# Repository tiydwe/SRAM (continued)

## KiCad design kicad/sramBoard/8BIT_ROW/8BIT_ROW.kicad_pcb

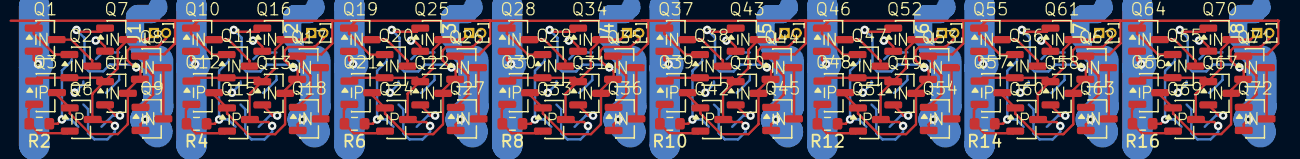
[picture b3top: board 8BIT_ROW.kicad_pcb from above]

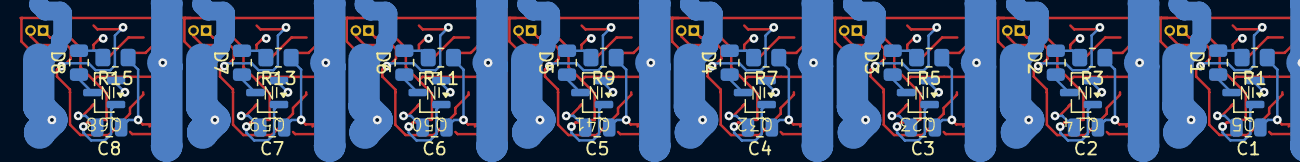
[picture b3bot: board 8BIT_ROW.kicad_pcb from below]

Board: 4 copper layers, 112 parts (32 on the bottom side), 59 nets.

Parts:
C1, C2, C3, C4, C5, C6, C7, C8: 100nC; C_0805_2012Metric
D1, D2, D3, D4, D5, D6, D7, D8: LED; C_0805_2012Metric
J1, J2, J3, J4, J5, J6, J7, J8: Conn_01x02_Pin; PinHeader_1x02_P1.00mm_Vertical
Q1, Q2, Q4, Q5, Q7, Q8, Q9, Q10, Q11, Q13, Q14, Q16, Q17, Q18, Q19, Q20, Q22, Q23, Q25, Q26, Q27, Q28, Q29, Q31, Q32, Q34, Q35, Q36, Q37, Q38, Q40, Q41, Q43, Q44, Q45, Q46, Q47, Q49, Q50, Q52, Q53, Q54, Q55, Q56, Q58, Q59, Q61, Q62, Q63, Q64, Q65, Q67, Q68, Q70, Q71, Q72: Q_NMOS_GSD; SOT-23-N
Q3, Q6, Q12, Q15, Q21, Q24, Q30, Q33, Q39, Q42, Q48, Q51, Q57, Q60, Q66, Q69: Q_PMOS_GSD; SOT-23-P
R1, R3, R5, R7, R9, R11, R13, R15: 360R; R_0805_2012Metric_Pad1.20x1.40mm_HandSolder
R2, R4, R6, R8, R10, R12, R14, R16: 47R; R_0603_1608Metric

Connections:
+5V: C1.1, C2.1, C3.1, C4.1, C5.1, C6.1, C7.1, C8.1, R1.1, R2.1, R3.1, R4.1, R5.1, R6.1, R7.1, R8.1, R9.1, R10.1, R11.1, R12.1, R13.1, R14.1, R15.1, R16.1
/WL: Q1.1 (G), Q2.1 (G), Q8.1 (G), Q9.1 (G), Q10.1 (G), Q11.1 (G), Q17.1 (G), Q18.1 (G), Q19.1 (G), Q20.1 (G), Q26.1 (G), Q27.1 (G), Q28.1 (G), Q29.1 (G), Q35.1 (G), Q36.1 (G), Q37.1 (G), Q38.1 (G), Q44.1 (G), Q45.1 (G), Q46.1 (G), Q47.1 (G), Q53.1 (G), Q54.1 (G), Q55.1 (G), Q56.1 (G), Q62.1 (G), Q63.1 (G), Q64.1 (G), Q65.1 (G), Q71.1 (G), Q72.1 (G)
GND: C1.2, C2.2, C3.2, C4.2, C5.2, C6.2, C7.2, C8.2, Q4.2 (S), Q5.2 (S), Q7.2 (S), Q13.2 (S), Q14.2 (S), Q16.2 (S), Q22.2 (S), Q23.2 (S), Q25.2 (S), Q31.2 (S), Q32.2 (S), Q34.2 (S), Q40.2 (S), Q41.2 (S), Q43.2 (S), Q49.2 (S), Q50.2 (S), Q52.2 (S), Q58.2 (S), Q59.2 (S), Q61.2 (S), Q67.2 (S), Q68.2 (S), Q70.2 (S)
unnamed: D1.2 (A), R1.2
unnamed: D1.1 (K), Q5.3 (D)
unnamed: D2.2 (A), R3.2
unnamed: D2.1 (K), Q14.3 (D)
unnamed: D3.2 (A), R5.2
unnamed: D3.1 (K), Q23.3 (D)
unnamed: D4.2 (A), R7.2
unnamed: D4.1 (K), Q32.3 (D)
unnamed: D5.2 (A), R9.2
unnamed: D5.1 (K), Q41.3 (D)
unnamed: D6.2 (A), R11.2
unnamed: D6.1 (K), Q50.3 (D)
unnamed: D7.2 (A), R13.2
unnamed: D7.1 (K), Q59.3 (D)
unnamed: D8.2 (A), R15.2
unnamed: D8.1 (K), Q68.3 (D)
unnamed: J1.1, Q2.2 (S), Q3.1 (G), Q4.1 (G), Q5.1 (G), Q6.3 (D), Q7.3 (D)
unnamed: J1.2, Q3.3 (D), Q4.3 (D), Q6.1 (G), Q7.1 (G), Q8.2 (S)
unnamed: J2.1, Q11.2 (S), Q12.1 (G), Q13.1 (G), Q14.1 (G), Q15.3 (D), Q16.3 (D)
unnamed: J2.2, Q12.3 (D), Q13.3 (D), Q15.1 (G), Q16.1 (G), Q17.2 (S)
unnamed: J3.1, Q20.2 (S), Q21.1 (G), Q22.1 (G), Q23.1 (G), Q24.3 (D), Q25.3 (D)
unnamed: J3.2, Q21.3 (D), Q22.3 (D), Q24.1 (G), Q25.1 (G), Q26.2 (S)
unnamed: J4.1, Q29.2 (S), Q30.1 (G), Q31.1 (G), Q32.1 (G), Q33.3 (D), Q34.3 (D)
unnamed: J4.2, Q30.3 (D), Q31.3 (D), Q33.1 (G), Q34.1 (G), Q35.2 (S)
unnamed: J5.1, Q38.2 (S), Q39.1 (G), Q40.1 (G), Q41.1 (G), Q42.3 (D), Q43.3 (D)
unnamed: J5.2, Q39.3 (D), Q40.3 (D), Q42.1 (G), Q43.1 (G), Q44.2 (S)
unnamed: J6.1, Q47.2 (S), Q48.1 (G), Q49.1 (G), Q50.1 (G), Q51.3 (D), Q52.3 (D)
unnamed: J6.2, Q48.3 (D), Q49.3 (D), Q51.1 (G), Q52.1 (G), Q53.2 (S)
unnamed: J7.1, Q56.2 (S), Q57.1 (G), Q58.1 (G), Q59.1 (G), Q60.3 (D), Q61.3 (D)
unnamed: J7.2, Q57.3 (D), Q58.3 (D), Q60.1 (G), Q61.1 (G), Q62.2 (S)
unnamed: J8.1, Q65.2 (S), Q66.1 (G), Q67.1 (G), Q68.1 (G), Q69.3 (D), Q70.3 (D)
unnamed: J8.2, Q66.3 (D), Q67.3 (D), Q69.1 (G), Q70.1 (G), Q71.2 (S)
unnamed: Q1.3 (D), Q2.3 (D)
unnamed: Q3.2 (S), Q6.2 (S), R2.2
unnamed: Q8.3 (D), Q9.3 (D)
unnamed: Q10.3 (D), Q11.3 (D)
unnamed: Q12.2 (S), Q15.2 (S), R4.2
unnamed: Q17.3 (D), Q18.3 (D)
unnamed: Q19.3 (D), Q20.3 (D)
unnamed: Q21.2 (S), Q24.2 (S), R6.2
unnamed: Q26.3 (D), Q27.3 (D)
unnamed: Q28.3 (D), Q29.3 (D)
unnamed: Q30.2 (S), Q33.2 (S), R8.2
unnamed: Q35.3 (D), Q36.3 (D)
unnamed: Q37.3 (D), Q38.3 (D)
unnamed: Q39.2 (S), Q42.2 (S), R10.2
unnamed: Q44.3 (D), Q45.3 (D)
unnamed: Q46.3 (D), Q47.3 (D)
unnamed: Q48.2 (S), Q51.2 (S), R12.2
unnamed: Q53.3 (D), Q54.3 (D)
unnamed: Q55.3 (D), Q56.3 (D)
unnamed: Q57.2 (S), Q60.2 (S), R14.2
unnamed: Q62.3 (D), Q63.3 (D)
unnamed: Q64.3 (D), Q65.3 (D)
unnamed: Q66.2 (S), Q69.2 (S), R16.2
unnamed: Q71.3 (D), Q72.3 (D)

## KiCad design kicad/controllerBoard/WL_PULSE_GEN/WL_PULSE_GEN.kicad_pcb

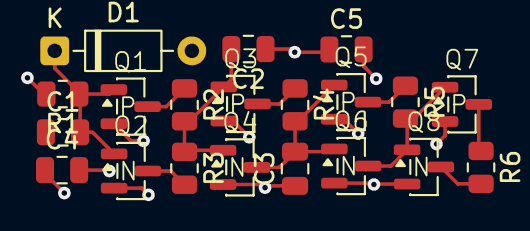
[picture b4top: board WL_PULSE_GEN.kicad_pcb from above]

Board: 2 copper layers, 20 parts (0 on the bottom side), 12 nets.

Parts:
C1, C2, C4, C5: 100nC; C_0805_2012Metric
C3: 4.7uC; C_0805_2012Metric
D1: 1N4148; D_DO-35_SOD27_P7.62mm_Horizontal
Q1, Q3, Q5, Q7: Q_PMOS_GSD; SOT-23-P
Q2, Q4, Q6, Q8: Q_NMOS_GSD; SOT-23-N
R1: 100kR; R_0805_2012Metric
R2, R5: 47R; R_0805_2012Metric
R3, R6: 4.7R; R_0805_2012Metric
R4: 4.7kR; R_0805_2012Metric

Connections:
+5V: C4.2, C5.2, Q1.2 (S), Q3.2 (S), Q5.2 (S), Q7.2 (S)
/WL_PULSE: Q8.3 (D), R6.2
GND: C2.1, C3.1, C4.1, C5.1, D1.2 (A), Q2.2 (S), Q4.2 (S), Q6.2 (S), Q8.2 (S), R1.2
unnamed: C1.2, D1.1 (K), Q1.1 (G), Q2.1 (G), R1.1
unnamed: Q1.3 (D), R2.1
unnamed: Q2.3 (D), R3.2
unnamed: Q3.3 (D), R4.1
unnamed: C2.2, Q3.1 (G), Q4.1 (G), R2.2, R3.1
unnamed: C3.2, Q4.3 (D), Q5.1 (G), Q6.1 (G), R4.2
unnamed: Q5.3 (D), R5.1
unnamed: Q6.3 (D), Q7.1 (G), Q8.1 (G), R5.2
unnamed: Q7.3 (D), R6.1

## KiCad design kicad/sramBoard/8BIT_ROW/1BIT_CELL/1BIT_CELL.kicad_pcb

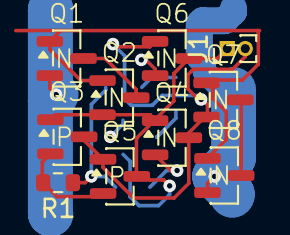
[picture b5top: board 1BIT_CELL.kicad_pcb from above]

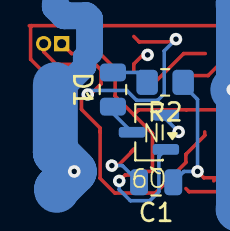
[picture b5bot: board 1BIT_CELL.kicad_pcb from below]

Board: 4 copper layers, 14 parts (4 on the bottom side), 10 nets.

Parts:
C1: 100nC; C_0805_2012Metric
D1: LED; C_0805_2012Metric
J1: Conn_01x02_Pin; PinHeader_1x02_P1.00mm_Vertical
Q1, Q2, Q4, Q6, Q7, Q8, Q9: Q_NMOS_GSD; SOT-23-N
Q3, Q5: Q_PMOS_GSD; SOT-23-P
R1: 47R; R_0603_1608Metric
R2: 360R; R_0805_2012Metric_Pad1.20x1.40mm_HandSolder

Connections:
+5V: C1.1, R1.1, R2.1
/WL: Q1.1 (G), Q2.1 (G), Q7.1 (G), Q8.1 (G)
GND: C1.2, Q4.2 (S), Q6.2 (S), Q9.2 (S)
unnamed: D1.2 (A), R2.2
unnamed: D1.1 (K), Q9.3 (D)
unnamed: J1.1, Q2.2 (S), Q3.1 (G), Q4.1 (G), Q5.3 (D), Q6.3 (D), Q9.1 (G)
unnamed: J1.2, Q3.3 (D), Q4.3 (D), Q5.1 (G), Q6.1 (G), Q7.2 (S)
unnamed: Q1.3 (D), Q2.3 (D)
unnamed: Q3.2 (S), Q5.2 (S), R1.2
unnamed: Q7.3 (D), Q8.3 (D)

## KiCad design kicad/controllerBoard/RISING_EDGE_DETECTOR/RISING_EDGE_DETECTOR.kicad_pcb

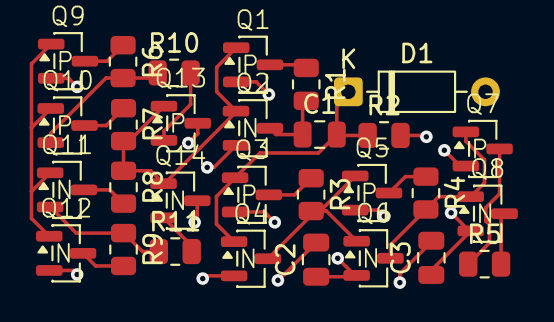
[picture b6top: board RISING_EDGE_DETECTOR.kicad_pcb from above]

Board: 2 copper layers, 29 parts (0 on the bottom side), 21 nets.

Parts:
C1, C2, C3: 100nC; C_0805_2012Metric
D1: 1N4148; D_DO-35_SOD27_P7.62mm_Horizontal
Q1, Q3, Q5, Q7, Q9, Q10, Q13: Q_PMOS_GSD; SOT-23-P
Q2, Q4, Q6, Q8, Q11, Q12, Q14: Q_NMOS_GSD; SOT-23-N
R1, R3, R5, R6, R7, R8, R9: 47R; R_0805_2012Metric
R2: 10kR; R_0805_2012Metric
R4: 1R; R_0805_2012Metric
R10, R11: 10R; R_0805_2012Metric

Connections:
+5V: C2.2, C3.2, Q1.2 (S), Q3.2 (S), Q5.2 (S), Q7.2 (S), Q9.2 (S), Q14.3 (D)
/SCHMITT_TRIGGER/V_{out}: Q1.1 (G), Q2.1 (G), Q13.1 (G), Q14.1 (G), R7.2, R8.1
/V_{in}: Q9.1 (G), Q10.1 (G), Q11.1 (G), Q12.1 (G)
/V_{pulse}: Q6.3 (D), Q7.1 (G), Q8.1 (G), R4.2
/~V_{pulse}: Q8.3 (D), R5.2
GND: C2.1, C3.1, D1.2 (A), Q2.2 (S), Q4.2 (S), Q6.2 (S), Q8.2 (S), Q12.2 (S), Q13.3 (D), R2.2
unnamed: C1.2, D1.1 (K), Q3.1 (G), Q4.1 (G), R2.1
unnamed: Q1.3 (D), R1.1
unnamed: C1.1, Q2.3 (D), R1.2
unnamed: Q3.3 (D), R3.1
unnamed: Q4.3 (D), Q5.1 (G), Q6.1 (G), R3.2
unnamed: Q5.3 (D), R4.1
unnamed: Q7.3 (D), R5.1
unnamed: Q9.3 (D), R6.1
unnamed: Q10.3 (D), R7.1
unnamed: Q10.2 (S), R6.2, R10.1
unnamed: Q11.3 (D), R8.2
unnamed: Q11.2 (S), R9.1, R11.1
unnamed: Q12.3 (D), R9.2
unnamed: Q13.2 (S), R10.2
unnamed: Q14.2 (S), R11.2

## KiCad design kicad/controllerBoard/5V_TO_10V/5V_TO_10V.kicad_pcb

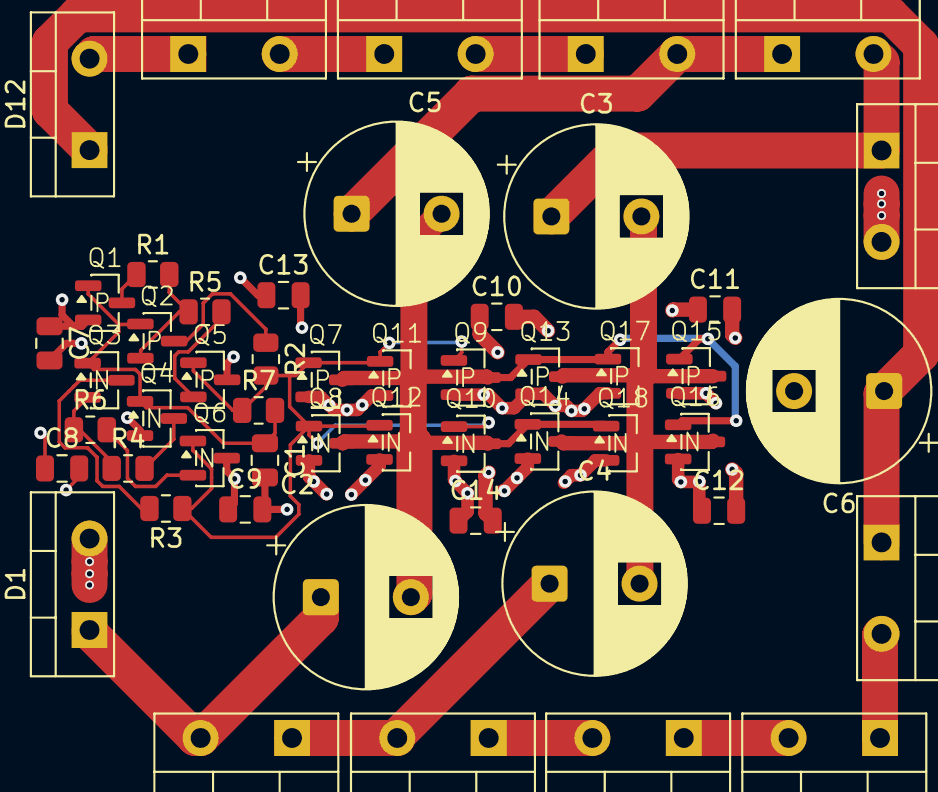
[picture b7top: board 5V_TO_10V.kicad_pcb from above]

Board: 2 copper layers, 51 parts (0 on the bottom side), 25 nets.

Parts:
C1, C7, C8, C9, C10, C11, C12, C13, C14: 100nC; C_0805_2012Metric
C2, C3, C4, C5, C6: C_Polarized; CP_Radial_D10.0mm_P5.00mm
D1, D2, D3, D4, D5, D6, D7, D8, D9, D10, D11, D12: MUR1560FAC; TO-220-2_Vertical
Q1, Q2, Q5, Q7, Q9, Q11, Q13, Q15, Q17: Q_PMOS_GSD; SOT-23-P
Q3, Q4, Q6, Q8, Q10, Q12, Q14, Q16, Q18: Q_NMOS_GSD; SOT-23-N
R1, R2, R3, R4: 47R; R_0805_2012Metric
R5, R6: 1R; R_0805_2012Metric
R7: 470R; R_0805_2012Metric

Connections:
+5V: C7.1, C8.1, C9.1, C10.1, C11.2, C12.2, C13.2, C14.2, D1.2 (A), D2.2 (A), Q1.2 (S), Q6.3 (D), Q7.2 (S), Q9.2 (S), Q11.2 (S), Q13.2 (S), Q15.2 (S), Q17.2 (S)
/10V: C6.1, D11.1 (K), D12.1 (K)
GND: C1.2, C6.2, C7.2, C8.2, C9.2, C10.2, C11.1, C12.1, C13.1, C14.1, Q4.2 (S), Q5.3 (D), Q8.2 (S), Q10.2 (S), Q12.2 (S), Q14.2 (S), Q16.2 (S), Q18.2 (S)
unnamed: C2.1, D1.1 (K), D3.2 (A)
unnamed: C3.1, D2.1 (K), D4.2 (A)
unnamed: C4.1, D3.1 (K), D5.2 (A)
unnamed: C5.1, D4.1 (K), D6.2 (A)
unnamed: D5.1 (K), D7.2 (A)
unnamed: D6.1 (K), D8.2 (A)
unnamed: D7.1 (K), D9.2 (A)
unnamed: D8.1 (K), D10.2 (A)
unnamed: D10.1 (K), D12.2 (A)
unnamed: D9.1 (K), D11.2 (A)
unnamed: Q1.3 (D), R1.1
unnamed: C1.1, Q1.1 (G), Q2.1 (G), Q3.1 (G), Q4.1 (G), R7.2
unnamed: Q2.3 (D), R2.1
unnamed: Q2.2 (S), R1.2, R5.1
unnamed: Q3.3 (D), R3.2
unnamed: Q3.2 (S), R4.1, R6.1
unnamed: Q4.3 (D), R4.2
unnamed: Q5.2 (S), R5.2
unnamed: Q6.2 (S), R6.2
unnamed: C2.2, C5.2, Q7.3 (D), Q8.3 (D), Q9.3 (D), Q10.3 (D), Q11.3 (D), Q12.3 (D), Q13.1 (G), Q14.1 (G), Q15.1 (G), Q16.1 (G), Q17.1 (G), Q18.1 (G)
unnamed: Q5.1 (G), Q6.1 (G), Q7.1 (G), Q8.1 (G), Q9.1 (G), Q10.1 (G), Q11.1 (G), Q12.1 (G), R2.2, R3.1, R7.1
unnamed: C3.2, C4.2, Q13.3 (D), Q14.3 (D), Q15.3 (D), Q16.3 (D), Q17.3 (D), Q18.3 (D)

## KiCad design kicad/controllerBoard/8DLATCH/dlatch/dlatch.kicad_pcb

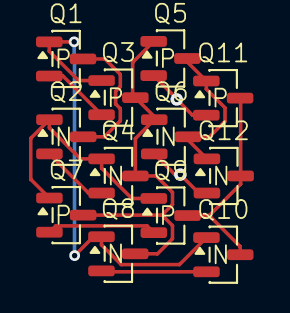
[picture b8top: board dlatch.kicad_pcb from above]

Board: 2 copper layers, 12 parts (0 on the bottom side), 12 nets.

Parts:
Q1, Q3, Q5, Q7, Q9, Q11: Q_PMOS_GSD; SOT-23-P
Q2, Q4, Q6, Q8, Q10, Q12: Q_NMOS_GSD; SOT-23-N

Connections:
+5V: Q5.2 (S), Q11.2 (S)
/D: Q1.3 (D), Q2.3 (D)
/EN: Q2.1 (G), Q4.1 (G), Q7.1 (G), Q9.1 (G)
/Q: Q9.3 (D), Q10.3 (D), Q11.3 (D), Q12.3 (D)
/~EN: Q1.1 (G), Q3.1 (G), Q8.1 (G), Q10.1 (G)
/~Q: Q5.3 (D), Q6.3 (D), Q11.1 (G), Q12.1 (G)
GND: Q6.2 (S), Q12.2 (S)
unnamed: Q1.2 (S), Q3.2 (S)
unnamed: Q2.2 (S), Q4.2 (S)
unnamed: Q3.3 (D), Q4.3 (D), Q5.1 (G), Q6.1 (G), Q7.3 (D), Q8.3 (D)
unnamed: Q7.2 (S), Q9.2 (S)
unnamed: Q8.2 (S), Q10.2 (S)
